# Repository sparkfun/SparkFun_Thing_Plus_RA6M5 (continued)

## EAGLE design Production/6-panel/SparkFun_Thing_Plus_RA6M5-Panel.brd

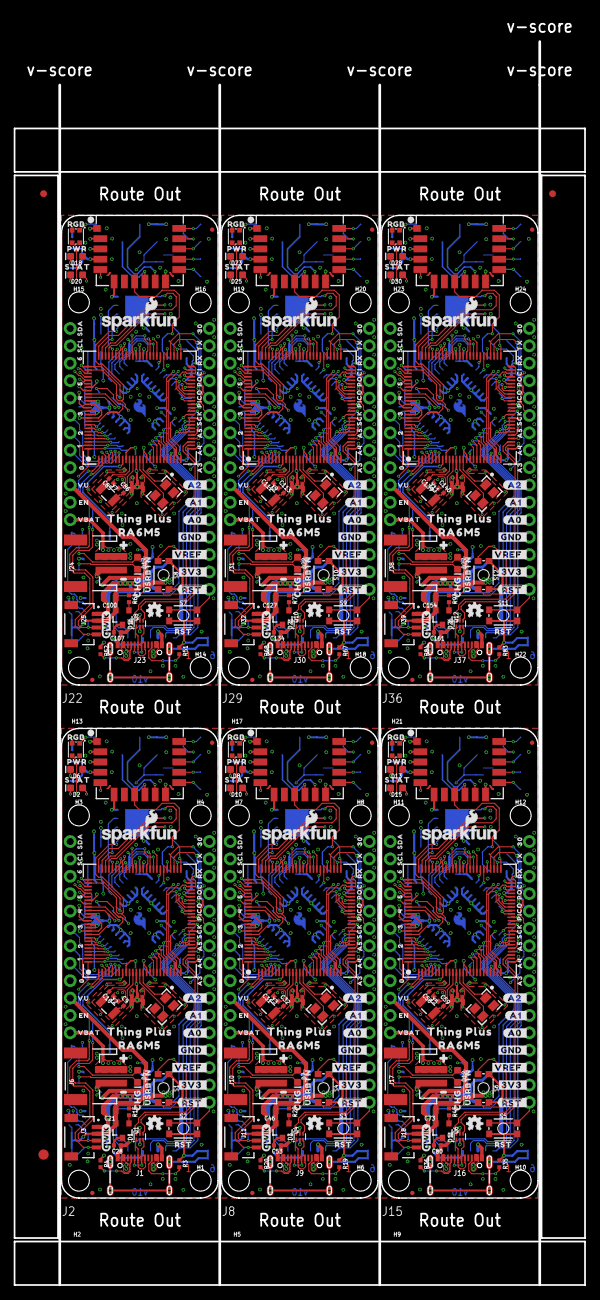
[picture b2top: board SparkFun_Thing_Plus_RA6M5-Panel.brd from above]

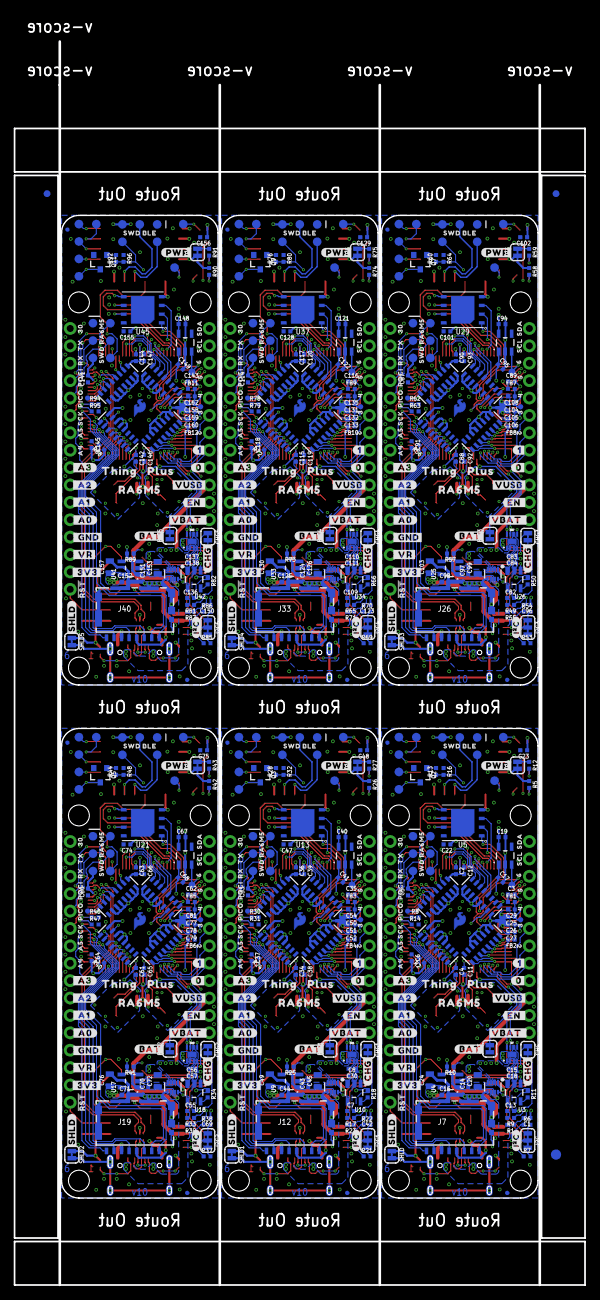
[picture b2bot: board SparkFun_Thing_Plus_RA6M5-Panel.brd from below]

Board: 6 copper layers, 83.3 x 181.6 mm, 1104 parts (657 on the bottom side), 702 nets.

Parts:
BAT, BAT1, BAT2, BAT3, BAT4, BAT5: JUMPER-SMT_2_NC_TRACE_SILK; SMT-JUMPER_2_NC_TRACE_SILK
C1, C19, C27, C29, C40, C42, C52, C54, C67, C69, C79, C81, C94, C96, C106, C108, C121, C123, C133, C135, C148, C150, C160, C162: 1.0uF; 0402-TIGHT
C2, C3, C4, C5, C6, C11, C12, C18, C22, C23, C25, C26, C28, C30, C33, C34, C35, C36, C37, C38, C39, C47, C48, C50, C51, C53, C57, C60, C61, C62, C63, C64, C65, C66, C74, C75, C77, C78, C80, C84, C87, C88, C89, C90, C91, C92, C93, C101, C102, C104, C105, C107, C111, C114, C115, C116, C117, C118, C119, C120, C128, C129, C131, C132, C134, C138, C141, C142, C143, C144, C145, C146, C147, C155, C156, C158, C159, C161: 0.1uF; 0402-TIGHT
C7, C8, C13, C14, C15, C16, C17, C41, C43, C44, C55, C56, C68, C70, C71, C82, C83, C95, C97, C98, C109, C110, C122, C124, C125, C136, C137, C149, C151, C152: 2.2uF; 0402-TIGHT
C9, C10, C31, C32, C58, C59, C85, C86, C112, C113, C139, C140: 9.1pF; 0402-TIGHT
C20, C21, C45, C46, C72, C73, C99, C100, C126, C127, C153, C154: 10uF; 0805
C24, C49, C76, C103, C130, C157: 47uF/6.3V; 0805
CHG, CHG1, CHG2, CHG3, CHG4, CHG5: JUMPER-SMT_2_NC_TRACE_SILK; SMT-JUMPER_2_NC_TRACE_SILK
D1, D3, D11, D16, D21, D26: PRTR5V0U2F; SOT886
D2, D10, D15, D20, D25, D30: BLUE; LED-0603
D4, D9, D14, D19, D24, D29: WS2812_2020; WS2812-2020
D5, D7, D12, D17, D22, D27: Yellow; LED-0603
D6, D8, D13, D18, D23, D28: LED-0603
E$1, E$2, E$3, E$4: FIDUCIAL-1X2
E$5, E$6: FIDUCIAL-1.5X3
FB1, FB2, FB3, FB4, FB5, FB6, FB7, FB8, FB9, FB10, FB11, FB12: 120-OHM; 0402-TIGHT
FD1, FD2, FD3, FD4, FD5, FD6, FD7, FD8, FD9, FD10, FD11, FD12, FD13, FD14, FD15, FD16, FD17, FD18, FD19, FD20, FD21, FD22, FD23, FD24: FIDUCIALUFIDUCIAL; FIDUCIAL-MICRO
FRAME1, FRAME2, FRAME3, FRAME4, FRAME5, FRAME6: FRAME-LEDGERNO_FOOTPRINT; DUMMY
H1, H2, H3, H4, H5, H6, H7, H8, H9, H10, H11, H12, H13, H14, H15, H16, H17, H18, H19, H20, H21, H22, H23, H24: STAND-OFFTIGHT; STAND-OFF-TIGHT
I2C, I2C1, I2C2, I2C3, I2C4, I2C5: JUMPER-SMT_3_2-NC_TRACE_SILK; SMT-JUMPER_3_2-NC_TRACE_SILK
J1, J9, J16, J23, J30, J37: USB Female Type C Connector; USB-C-16P-6LAYER-ISOLATED
J2, J8, J15, J22, J29, J36: THING_PLUS_LOGICAL; THING_PLUS
J3, J11, J18, J25, J32, J39: QWIIC_RA; JST04_1MM_RA
J4, J13, J20, J27, J34, J41: CONN_03X2; PAD_05_03X2_TP
J5, J14, J21, J28, J35, J42: PAD_05_03X2_TP_NO4
J6, J10, J17, J24, J31, J38: JST-2-SMD
J7, J12, J19, J26, J33, J40: MICRO-SDFRICTION; MICROSD_TINY
JP1, JP2, JP3, JP4, JP5, JP6: JUMPER-SMT_2_NC_TRACE_SILK; SMT-JUMPER_2_NC_TRACE_SILK
LOGO1, LOGO7, LOGO11, LOGO15, LOGO19, LOGO23: OSHW-LOGOMINI; OSHW-LOGO-MINI
LOGO2, LOGO5, LOGO9, LOGO13, LOGO17, LOGO21: SFE_LOGO_NAME_FLAME.1_INCH; SFE_LOGO_NAME_FLAME_.1
LOGO3, LOGO6, LOGO10, LOGO14, LOGO18, LOGO22: QWIIC_LOGO_4MM; QWIIC_4MM
LOGO4, LOGO8, LOGO12, LOGO16, LOGO20, LOGO24: SFE_LOGO_NAME_FLAMEBLANK; BLANK
Q1, Q2, Q3, Q4, Q5, Q6, Q7, Q8, Q9, Q10, Q11, Q12: 20V/4.2A/52mΩ/1.4W; SOT23-3
R1, R13, R15, R23, R28, R29, R39, R44, R45, R55, R60, R61, R71, R76, R77, R87, R92, R93: 1k; 0402-TIGHT
R2, R24, R40, R56, R72, R88: 20k; 0402-TIGHT
R3, R4, R19, R20, R35, R36, R51, R52, R67, R68, R83, R84: 5.1k; 0402-TIGHT
R5, R6, R7, R21, R22, R26, R37, R38, R42, R53, R54, R58, R69, R70, R74, R85, R86, R90: 2.2k; 0402-TIGHT
R8, R14, R16, R30, R31, R32, R46, R47, R48, R62, R63, R64, R78, R79, R80, R94, R95, R96: 10k; 0402-TIGHT
R9, R11, R12, R17, R18, R27, R33, R34, R43, R49, R50, R59, R65, R66, R75, R81, R82, R91: 4.7k; 0402-TIGHT
R10, R25, R41, R57, R73, R89: 1M; 0402-TIGHT
RN1, RN2, RN3, RN4, RN5, RN6, RN7, RN8, RN9, RN10, RN11, RN12, RN13, RN14, RN15, RN16, RN17, RN18, RN19, RN20, RN21, RN22, RN23, RN24: 10K; 2506_AR
S1, S4, S6, S8, S10, S12: USER; TACTILE_SWITCH_SMD_4.6X2.8MM
S2, S3, S5, S7, S9, S11: RESET; TACTILE_SWITCH_SMD_4.6X2.8MM
SHLD, SHLD1, SHLD2, SHLD3, SHLD4, SHLD5: JUMPER-SMT_2_NC_TRACE_SILK; SMT-JUMPER_2_NC_TRACE_SILK
SUPPLYTIE1, SUPPLYTIE2, SUPPLYTIE3, SUPPLYTIE4, SUPPLYTIE5, SUPPLYTIE6, SUPPLYTIE7, SUPPLYTIE8, SUPPLYTIE9, SUPPLYTIE10, SUPPLYTIE11, SUPPLYTIE12, SUPPLYTIE13, SUPPLYTIE14, SUPPLYTIE15, SUPPLYTIE16, SUPPLYTIE17, SUPPLYTIE18: 2PT_GND_TIESMALL; 2PT_GND_TIE_SMALL
TP1, TP3, TP5, TP6, TP7, TP8, TP10, TP11, TP13, TP15, TP16, TP17, TP18, TP20, TP21, TP23, TP25, TP26, TP27, TP28, TP30, TP31, TP33, TP35, TP36, TP37, TP38, TP40, TP41, TP43, TP45, TP46, TP47, TP48, TP50, TP51, TP53, TP55, TP56, TP57, TP58, TP60: TEST-POINT3X5; PAD.03X.05
TP2, TP12, TP22, TP32, TP42, TP52: TEST-POINT3X4; PAD.03X.04
TP4, TP9, TP14, TP19, TP24, TP29, TP34, TP39, TP44, TP49, TP54, TP59: TEST-POINT3; PAD.03X.03
U1, U14, U22, U30, U38, U46: R7FA6M5; P-LQFP100-14X14-0.50
U2, U12, U20, U28, U36, U44: DA14531MOD
U3, U10, U18, U26, U34, U42: MCP73831; SOT23-5
U4, U6, U9, U15, U17, U23, U25, U31, U33, U39, U41, U47: RT9080-33GJ5; SOT23-5
U5, U13, U21, U29, U37, U45: MX25L12833F 128Mb; WSON-8-6X5
U7, U11, U19, U27, U35, U43: MAX17048; DFN-8
U8, U16, U24, U32, U40, U48: LM66200; SOT8
U$1, U$3, U$155, U$232, U$309, U$386: #I�C#0
U$2, U$4, U$156, U$233, U$310, U$387: #CHG#0
U$5, U$8, U$157, U$234, U$311, U$388: SFE_LOGO_FLAME_COPPER_EXPOSED_.1
U$6, U$13, U$51, U$109, U$158, U$186, U$235, U$263, U$312, U$340, U$389, U$417: #RST#0
U$7, U$14, U$159, U$236, U$313, U$390: CHG0
U$9, U$130, U$207, U$284, U$361, U$438: SWD_RA6M50
U$10, U$131, U$208, U$285, U$362, U$439: SWD_BLE0
U$11, U$15, U$160, U$237, U$314, U$391: STAT0
U$12, U$86, U$137, U$138, U$214, U$215, U$291, U$292, U$368, U$369, U$445, U$446: 300
U$16, U$74, U$161, U$238, U$315, U$392: PWR0
U$17, U$75, U$162, U$239, U$316, U$393: RGB0
U$18, U$128, U$205, U$282, U$359, U$436: THING_PLUS0
U$19, U$80, U$163, U$240, U$317, U$394: ##RST#_#0
U$20, U$87, U$164, U$241, U$318, U$395: #3V3_#0
U$21, U$88, U$165, U$242, U$319, U$396: #VREF_#0
U$22, U$89, U$166, U$243, U$320, U$397: #GND_#0
U$23, U$90, U$167, U$244, U$321, U$398: #A0_#0
U$24, U$91, U$168, U$245, U$322, U$399: #A1_#0
U$25, U$92, U$169, U$246, U$323, U$400: #A2_#0
U$26, U$93, U$170, U$247, U$324, U$401: A30
U$27, U$59, U$94, U$116, U$171, U$193, U$248, U$270, U$325, U$347, U$402, U$424: A40
U$28, U$60, U$95, U$117, U$172, U$194, U$249, U$271, U$326, U$348, U$403, U$425: A50
U$29, U$61, U$96, U$118, U$173, U$195, U$250, U$272, U$327, U$349, U$404, U$426: SCK0
U$30, U$62, U$97, U$119, U$174, U$196, U$251, U$273, U$328, U$350, U$405, U$427: PICO0
U$31, U$63, U$98, U$120, U$175, U$197, U$252, U$274, U$329, U$351, U$406, U$428: POCI0
U$32, U$64, U$99, U$121, U$176, U$198, U$253, U$275, U$330, U$352, U$407, U$429: RX0
U$33, U$65, U$100, U$122, U$177, U$199, U$254, U$276, U$331, U$353, U$408, U$430: TX0
U$34, U$43, U$139, U$146, U$216, U$223, U$293, U$300, U$370, U$377, U$447, U$454: 60
U$35, U$67, U$101, U$123, U$178, U$200, U$255, U$277, U$332, U$354, U$409, U$431: SDA0
U$36, U$68, U$102, U$124, U$179, U$201, U$256, U$278, U$333, U$355, U$410, U$432: SCL0
U$37, U$48, U$140, U$147, U$217, U$224, U$294, U$301, U$371, U$378, U$448, U$455: 50
U$38, U$66, U$141, U$148, U$218, U$225, U$295, U$302, U$372, U$379, U$449, U$456: 40
U$39, U$69, U$142, U$149, U$219, U$226, U$296, U$303, U$373, U$380, U$450, U$457: 30
U$40, U$70, U$143, U$150, U$220, U$227, U$297, U$304, U$374, U$381, U$451, U$458: 20
U$41, U$144, U$221, U$298, U$375, U$452: 10
U$42, U$145, U$222, U$299, U$376, U$453: 00
U$44, U$103, U$180, U$257, U$334, U$411: VU0
U$45, U$104, U$181, U$258, U$335, U$412: EN0
U$46, U$105, U$182, U$259, U$336, U$413: VBAT0
U$47, U$106, U$183, U$260, U$337, U$414: #PWR#0
U$49, U$107, U$184, U$261, U$338, U$415: #BAT#0
U$50, U$108, U$185, U$262, U$339, U$416: #SHLD#0
U$52, U$110, U$187, U$264, U$341, U$418: #_3V3#0
U$53, U$154, U$231, U$308, U$385, U$462: #_VR#0
U$54, U$111, U$188, U$265, U$342, U$419: #_GND#0
U$55, U$112, U$189, U$266, U$343, U$420: #_A0#0
U$56, U$113, U$190, U$267, U$344, U$421: #_A1#0
U$57, U$114, U$191, U$268, U$345, U$422: #_A2#0
U$58, U$115, U$192, U$269, U$346, U$423: #_A3#0
U$71, U$151, U$228, U$305, U$382, U$459: #1#0
U$72, U$152, U$229, U$306, U$383, U$460: #0#0
U$73, U$153, U$230, U$307, U$384, U$461: #USRBTN#0
U$76, U$125, U$202, U$279, U$356, U$433: #VUSB#0
U$77, U$126, U$203, U$280, U$357, U$434: #EN_#0
U$78, U$127, U$204, U$281, U$358, U$435: #VBAT_#0
U$79, U$82, U$129, U$132, U$206, U$209, U$283, U$286, U$360, U$363, U$437, U$440: RA6M50
U$81, U$135, U$212, U$289, U$366, U$443: #0
U$83, U$133, U$210, U$287, U$364, U$441: THING0
U$84, U$134, U$211, U$288, U$365, U$442: PLUS0
U$85, U$136, U$213, U$290, U$367, U$444: _#0
Y1, Y4, Y6, Y8, Y10, Y12: 24.000MHz; 4-SMD,32X25
Y2, Y3, Y5, Y7, Y9, Y11: 32.768kHz; CRYSTAL-SMD-3.2X1.5MM

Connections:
3.3V: BAT.1, C2.1, C3.1, C4.1, C5.1, C6.1, C16.1, C21.1, C22.2, C23.2, C24.1, D4.VCC, D6.A, FB1.1, I2C.2, J2.27, J3.2, J4.1, J5.1, Q1.2, Q2.2, R8.2, R14.2, R16.1, RN1.10, RN1.11, RN3.1, RN3.2, RN3.3, RN4.1, RN5.15, RN5.16, U1.15, U1.29, U1.46, U1.62, U1.82, U2.7, U4.5, U5.8
3.3V1: BAT1.1, C33.1, C34.1, C35.1, C36.1, C37.1, C44.1, C46.1, C47.2, C48.2, C49.1, D8.A, D9.VCC, FB3.1, I2C1.2, J8.27, J11.2, J13.1, J14.1, Q3.2, Q4.2, R30.2, R31.2, R32.1, RN2.1, RN6.10, RN6.11, RN7.15, RN7.16, RN8.1, RN8.2, RN8.3, U9.5, U12.7, U13.8, U14.15, U14.29, U14.46, U14.62, U14.82
3.3V2: BAT2.1, C60.1, C61.1, C62.1, C63.1, C64.1, C71.1, C73.1, C74.2, C75.2, C76.1, D13.A, D14.VCC, FB5.1, I2C2.2, J15.27, J18.2, J20.1, J21.1, Q5.2, Q6.2, R46.2, R47.2, R48.1, RN9.1, RN10.10, RN10.11, RN11.15, RN11.16, RN12.1, RN12.2, RN12.3, U17.5, U20.7, U21.8, U22.15, U22.29, U22.46, U22.62, U22.82
3.3V3: BAT3.1, C87.1, C88.1, C89.1, C90.1, C91.1, C98.1, C100.1, C101.2, C102.2, C103.1, D18.A, D19.VCC, FB7.1, I2C3.2, J22.27, J25.2, J27.1, J28.1, Q7.2, Q8.2, R62.2, R63.2, R64.1, RN13.1, RN14.10, RN14.11, RN15.15, RN15.16, RN16.1, RN16.2, RN16.3, U25.5, U28.7, U29.8, U30.15, U30.29, U30.46, U30.62, U30.82
3.3V4: BAT4.1, C114.1, C115.1, C116.1, C117.1, C118.1, C125.1, C127.1, C128.2, C129.2, C130.1, D23.A, D24.VCC, FB9.1, I2C4.2, J29.27, J32.2, J34.1, J35.1, Q9.2, Q10.2, R78.2, R79.2, R80.1, RN17.1, RN18.10, RN18.11, RN19.15, RN19.16, RN20.1, RN20.2, RN20.3, U33.5, U36.7, U37.8, U38.15, U38.29, U38.46, U38.62, U38.82
3.3V5: BAT5.1, C141.1, C142.1, C143.1, C144.1, C145.1, C152.1, C154.1, C155.2, C156.2, C157.1, D28.A, D29.VCC, FB11.1, I2C5.2, J36.27, J39.2, J41.1, J42.1, Q11.2, Q12.2, R94.2, R95.2, R96.1, RN21.1, RN22.10, RN22.11, RN23.15, RN23.16, RN24.1, RN24.2, RN24.3, U41.5, U44.7, U45.8, U46.15, U46.29, U46.46, U46.62, U46.82
3.3V_SW: C28.2, J7.4, Q1.3
3.3V_SW1: C53.2, J12.4, Q4.3
3.3V_SW2: C80.2, J19.4, Q6.3
3.3V_SW3: C107.2, J26.4, Q8.3
3.3V_SW4: C134.2, J33.4, Q10.3
3.3V_SW5: C161.2, J40.4, Q12.3
!CTS_RA6/RTS_DA14531!: TP7.1, U1.47, U2.13
!CTS_RA6/RTS_DA14531!1: TP17.1, U12.13, U14.47
!CTS_RA6/RTS_DA14531!2: TP27.1, U20.13, U22.47
!CTS_RA6/RTS_DA14531!3: TP37.1, U28.13, U30.47
!CTS_RA6/RTS_DA14531!4: TP47.1, U36.13, U38.47
!CTS_RA6/RTS_DA14531!5: TP57.1, U44.13, U46.47
!DA14531_RST!: J5.6, R13.1, R16.2, U1.58
!DA14531_RST!1: J14.6, R28.1, R32.2, U14.58
!DA14531_RST!2: J21.6, R44.1, R48.2, U22.58
!DA14531_RST!3: J28.6, R60.1, R64.2, U30.58
!DA14531_RST!4: J35.6, R76.1, R80.2, U38.58
!DA14531_RST!5: J42.6, R92.1, R96.2, U46.58
!FG_ALRT!: RN5.1, U1.100, U7.5
!FG_ALRT!1: RN7.1, U11.5, U14.100
!FG_ALRT!2: RN11.1, U19.5, U22.100
!FG_ALRT!3: RN15.1, U27.5, U30.100
!FG_ALRT!4: RN19.1, U35.5, U38.100
!FG_ALRT!5: RN23.1, U43.5, U46.100
!NMI!: RN4.16, TP9.1, U1.40
!NMI!1: RN2.16, TP19.1, U14.40
!NMI!2: RN9.16, TP29.1, U22.40
!NMI!3: RN13.16, TP39.1, U30.40
!NMI!4: RN17.16, TP49.1, U38.40
!NMI!5: RN21.16, TP59.1, U46.40
!QCS!: RN1.7, U1.77, U5.1
!QCS!1: RN6.7, U13.1, U14.77
!QCS!2: RN10.7, U21.1, U22.77
!QCS!3: RN14.7, U29.1, U30.77
!QCS!4: RN18.7, U37.1, U38.77
!QCS!5: RN22.7, U45.1, U46.77
!RA6M5_RESET!: J2.28, J4.6, R14.1, S2.3, S2.4, U1.38, U2.8
!RA6M5_RESET!1: J8.28, J13.6, R31.1, S3.3, S3.4, U12.8, U14.38
!RA6M5_RESET!2: J15.28, J20.6, R47.1, S5.3, S5.4, U20.8, U22.38
!RA6M5_RESET!3: J22.28, J27.6, R63.1, S7.3, S7.4, U28.8, U30.38
!RA6M5_RESET!4: J29.28, J34.6, R79.1, S9.3, S9.4, U36.8, U38.38
!RA6M5_RESET!5: J36.28, J41.6, R95.1, S11.3, S11.4, U44.8, U46.38
!RTS_RA6/CTS_DA14531!: TP8.1, U1.49, U2.16
!RTS_RA6/CTS_DA14531!1: TP18.1, U12.16, U14.49
!RTS_RA6/CTS_DA14531!2: TP28.1, U20.16, U22.49
!RTS_RA6/CTS_DA14531!3: TP38.1, U28.16, U30.49
!RTS_RA6/CTS_DA14531!4: TP48.1, U36.16, U38.49
!RTS_RA6/CTS_DA14531!5: TP58.1, U44.16, U46.49
!SD_EN!: R15.1, RN3.16, U1.16
!SD_EN!1: R29.1, RN8.16, U14.16
!SD_EN!2: R45.1, RN12.16, U22.16
!SD_EN!3: R61.1, RN16.16, U30.16
!SD_EN!4: R77.1, RN20.16, U38.16
!SD_EN!5: R93.1, RN24.16, U46.16
!USR_BTN!: RN3.15, S1.1, S1.2, U1.17
!USR_BTN!1: RN8.15, S4.1, S4.2, U14.17
!USR_BTN!2: RN12.15, S6.1, S6.2, U22.17
!USR_BTN!3: RN16.15, S8.1, S8.2, U30.17
!USR_BTN!4: RN20.15, S10.1, S10.2, U38.17
!USR_BTN!5: RN24.15, S12.1, S12.2, U46.17
A0/DAC0/D1: J8.24, U14.85
A0/DAC0/D2: J15.24, U22.85
A0/DAC0/D3: J22.24, U30.85
A0/DAC0/D4: J29.24, U38.85
A0/DAC0/D5: J36.24, U46.85
A0/DAC0/D7: J2.24, U1.85
A1/DAC1/D1: J8.23, U14.84
A1/DAC1/D2: J15.23, U22.84
A1/DAC1/D3: J22.23, U30.84
A1/DAC1/D4: J29.23, U38.84
A1/DAC1/D5: J36.23, U46.84
A1/DAC1/D8: J2.23, U1.84
A2/D1: J8.22, U14.81
A2/D2: J15.22, U22.81
A2/D3: J22.22, U30.81
A2/D4: J29.22, U38.81
A2/D5: J36.22, U46.81
A2/D9: J2.22, U1.81
A3/D1: J8.21, U14.80
A3/D2: J15.21, U22.80
A3/D3: J22.21, U30.80
A3/D4: J29.21, U38.80
A3/D5: J36.21, U46.80
A3/D10: J2.21, U1.80
A4/D1: J8.20, U14.79
A4/D2: J15.20, U22.79
A4/D3: J22.20, U30.79
A4/D4: J29.20, U38.79
A4/D5: J36.20, U46.79
A4/D11: J2.20, U1.79
A5/D1: J8.19, U14.78
A5/D2: J15.19, U22.78
A5/D3: J22.19, U30.78
A5/D4: J29.19, U38.78
A5/D5: J36.19, U46.78
A5/D12: J2.19, U1.78
AGND: C25.2, C26.2, C27.2, C29.2, SUPPLYTIE1.P$1, U1.86, U1.89, U1.90
AGND1: C50.2, C51.2, C52.2, C54.2, SUPPLYTIE6.P$1, U14.86, U14.89, U14.90
AGND2: C77.2, C78.2, C79.2, C81.2, SUPPLYTIE9.P$1, U22.86, U22.89, U22.90
AGND3: C104.2, C105.2, C106.2, C108.2, SUPPLYTIE12.P$1, U30.86, U30.89, U30.90
AGND4: C131.2, C132.2, C133.2, C135.2, SUPPLYTIE15.P$1, U38.86, U38.89, U38.90
AGND5: C158.2, C159.2, C160.2, C162.2, SUPPLYTIE18.P$1, U46.86, U46.89, U46.90
AVCC0: C25.1, C29.1, FB1.2, TP4.1, U1.88
AVCC1: C50.1, C54.1, FB3.2, TP14.1, U14.88
AVCC2: C77.1, C81.1, FB5.2, TP24.1, U22.88
AVCC3: C104.1, C108.1, FB7.2, TP34.1, U30.88
AVCC4: C131.1, C135.1, FB9.2, TP44.1, U38.88
AVCC5: C158.1, C162.1, FB11.2, TP54.1, U46.88
BAT_SW: RN5.2, U1.99, U8.8
BAT_SW1: RN7.2, U14.99, U16.8
BAT_SW2: RN11.2, U22.99, U24.8
BAT_SW3: RN15.2, U30.99, U32.8
BAT_SW4: RN19.2, U38.99, U40.8
BAT_SW5: RN23.2, U46.99, U48.8
BLE_RST: Q2.3, TP3.1, U2.12
BLE_RST1: Q3.3, TP13.1, U12.12
BLE_RST2: Q5.3, TP23.1, U20.12
BLE_RST3: Q7.3, TP33.1, U28.12
BLE_RST4: Q9.3, TP43.1, U36.12
BLE_RST5: Q11.3, TP53.1, U44.12
BOOT/MD: R8.1, TP10.1, U1.39, U2.15
BOOT/MD1: R30.1, TP20.1, U12.15, U14.39
BOOT/MD2: R46.1, TP30.1, U20.15, U22.39
BOOT/MD3: R62.1, TP40.1, U28.15, U30.39
BOOT/MD4: R78.1, TP50.1, U36.15, U38.39
BOOT/MD5: R94.1, TP60.1, U44.15, U46.39
DA14531_SWCLK: J5.3, U2.10
DA14531_SWCLK1: J14.3, U12.10
DA14531_SWCLK2: J21.3, U20.10
DA14531_SWCLK3: J28.3, U28.10
DA14531_SWCLK4: J35.3, U36.10
DA14531_SWCLK5: J42.3, U44.10
DA14531_SWDIO: J5.2, U2.9
DA14531_SWDIO1: J14.2, U12.9
DA14531_SWDIO2: J21.2, U20.9
DA14531_SWDIO3: J28.2, U28.9
DA14531_SWDIO4: J35.2, U36.9
DA14531_SWDIO5: J42.2, U44.9
EXTAL: U1.14, Y1.1
EXTAL1: U14.14, Y4.1
EXTAL2: U22.14, Y6.1
EXTAL3: U30.14, Y8.1
EXTAL4: U38.14, Y10.1
EXTAL5: U46.14, Y12.1
FREE/D1: J8.13, U14.44
FREE/D2: J15.13, U22.44
FREE/D3: J22.13, U30.44
FREE/D4: J29.13, U38.44
FREE/D5: J36.13, U46.44
FREE/D30: J2.13, U1.44
GND: C1.1, C2.2, C3.2, C4.2, C5.2, C6.2, C11.2, C12.2, C13.2, C14.2, C15.2, C16.2, C17.2, C18.1, C19.2, C20.2, C21.2, C22.1, C23.1, C24.2, C28.1, D1.2, D4.GND, J1.GND, J1.GND2, J2.25, J3.1, J4.5, J5.5, J6.1, J7.6, J7.GND1, J7.GND2, J7.GND3, J7.GND4, J7.GND5, J7.GND6, JP4.1, R2.1, R3.1, R4.1, R5.1, R11.1, RN1.1, RN1.2, RN1.3, RN1.4, RN1.5, RN1.8, RN3.4, RN3.5, RN3.6, RN3.8, RN4.2, RN4.3, RN4.4, RN4.5, RN4.6, RN4.7, RN4.8, RN4.9, RN5.9, RN5.10, RN5.11, RN5.12, RN5.13, RN5.14, S1.3, S1.4, S2.1, S2.2, SHLD.1, SUPPLYTIE1.P$2, SUPPLYTIE2.P$2, SUPPLYTIE3.P$1, U1.12, U1.26, U1.45, U1.63, U1.83, U2.1, U2.2, U2.3, U2.4, U2.6, U2.11, U3.2, U4.2, U5.4, U6.2, U7.1, U7.4, U7.6, U7.9, U8.1, U8.4, U8.5
GND1: C7.2, C8.2, C30.1, C33.2, C34.2, C35.2, C36.2, C37.2, C38.2, C39.2, C40.2, C41.2, C42.1, C43.2, C44.2, C45.2, C46.2, C47.1, C48.1, C49.2, C53.1, D3.2, D9.GND, J8.25, J9.GND, J9.GND2, J10.1, J11.1, J12.6, J12.GND1, J12.GND2, J12.GND3, J12.GND4, J12.GND5, J12.GND6, J13.5, J14.5, JP1.1, R18.1, R19.1, R20.1, R24.1, R26.1, RN2.2, RN2.3, RN2.4, RN2.5, RN2.6, RN2.7, RN2.8, RN2.9, RN6.1, RN6.2, RN6.3, RN6.4, RN6.5, RN6.8, RN7.9, RN7.10, RN7.11, RN7.12, RN7.13, RN7.14, RN8.4, RN8.5, RN8.6, RN8.8, S3.1, S3.2, S4.3, S4.4, SHLD1.1, SUPPLYTIE4.P$1, SUPPLYTIE5.P$2, SUPPLYTIE6.P$2, U9.2, U10.2, U11.1, U11.4, U11.6, U11.9, U12.1, U12.2, U12.3, U12.4, U12.6, U12.11, U13.4, U14.12, U14.26, U14.45, U14.63, U14.83, U15.2, U16.1, U16.4, U16.5
GND2: C55.2, C56.2, C57.1, C60.2, C61.2, C62.2, C63.2, C64.2, C65.2, C66.2, C67.2, C68.2, C69.1, C70.2, C71.2, C72.2, C73.2, C74.1, C75.1, C76.2, C80.1, D11.2, D14.GND, J15.25, J16.GND, J16.GND2, J17.1, J18.1, J19.6, J19.GND1, J19.GND2, J19.GND3, J19.GND4, J19.GND5, J19.GND6, J20.5, J21.5, JP2.1, R34.1, R35.1, R36.1, R40.1, R42.1, RN9.2, RN9.3, RN9.4, RN9.5, RN9.6, RN9.7, RN9.8, RN9.9, RN10.1, RN10.2, RN10.3, RN10.4, RN10.5, RN10.8, RN11.9, RN11.10, RN11.11, RN11.12, RN11.13, RN11.14, RN12.4, RN12.5, RN12.6, RN12.8, S5.1, S5.2, S6.3, S6.4, SHLD2.1, SUPPLYTIE7.P$1, SUPPLYTIE8.P$2, SUPPLYTIE9.P$2, U17.2, U18.2, U19.1, U19.4, U19.6, U19.9, U20.1, U20.2, U20.3, U20.4, U20.6, U20.11, U21.4, U22.12, U22.26, U22.45, U22.63, U22.83, U23.2, U24.1, U24.4, U24.5
GND3: C82.2, C83.2, C84.1, C87.2, C88.2, C89.2, C90.2, C91.2, C92.2, C93.2, C94.2, C95.2, C96.1, C97.2, C98.2, C99.2, C100.2, C101.1, C102.1, C103.2, C107.1, D16.2, D19.GND, J22.25, J23.GND, J23.GND2, J24.1, J25.1, J26.6, J26.GND1, J26.GND2, J26.GND3, J26.GND4, J26.GND5, J26.GND6, J27.5, J28.5, JP3.1, R50.1, R51.1, R52.1, R56.1, R58.1, RN13.2, RN13.3, RN13.4, RN13.5, RN13.6, RN13.7, RN13.8, RN13.9, RN14.1, RN14.2, RN14.3, RN14.4, RN14.5, RN14.8, RN15.9, RN15.10, RN15.11, RN15.12, RN15.13, RN15.14, RN16.4, RN16.5, RN16.6, RN16.8, S7.1, S7.2, S8.3, S8.4, SHLD3.1, SUPPLYTIE10.P$1, SUPPLYTIE11.P$2, SUPPLYTIE12.P$2, U25.2, U26.2, U27.1, U27.4, U27.6, U27.9, U28.1, U28.2, U28.3, U28.4, U28.6, U28.11, U29.4, U30.12, U30.26, U30.45, U30.63, U30.83, U31.2, U32.1, U32.4, U32.5
GND4: C109.2, C110.2, C111.1, C114.2, C115.2, C116.2, C117.2, C118.2, C119.2, C120.2, C121.2, C122.2, C123.1, C124.2, C125.2, C126.2, C127.2, C128.1, C129.1, C130.2, C134.1, D21.2, D24.GND, J29.25, J30.GND, J30.GND2, J31.1, J32.1, J33.6, J33.GND1, J33.GND2, J33.GND3, J33.GND4, J33.GND5, J33.GND6, J34.5, J35.5, JP5.1, R66.1, R67.1, R68.1, R72.1, R74.1, RN17.2, RN17.3, RN17.4, RN17.5, RN17.6, RN17.7, RN17.8, RN17.9, RN18.1, RN18.2, RN18.3, RN18.4, RN18.5, RN18.8, RN19.9, RN19.10, RN19.11, RN19.12, RN19.13, RN19.14, RN20.4, RN20.5, RN20.6, RN20.8, S9.1, S9.2, S10.3, S10.4, SHLD4.1, SUPPLYTIE13.P$1, SUPPLYTIE14.P$2, SUPPLYTIE15.P$2, U33.2, U34.2, U35.1, U35.4, U35.6, U35.9, U36.1, U36.2, U36.3, U36.4, U36.6, U36.11, U37.4, U38.12, U38.26, U38.45, U38.63, U38.83, U39.2, U40.1, U40.4, U40.5
GND5: C136.2, C137.2, C138.1, C141.2, C142.2, C143.2, C144.2, C145.2, C146.2, C147.2, C148.2, C149.2, C150.1, C151.2, C152.2, C153.2, C154.2, C155.1, C156.1, C157.2, C161.1, D26.2, D29.GND, J36.25, J37.GND, J37.GND2, J38.1, J39.1, J40.6, J40.GND1, J40.GND2, J40.GND3, J40.GND4, J40.GND5, J40.GND6, J41.5, J42.5, JP6.1, R82.1, R83.1, R84.1, R88.1, R90.1, RN21.2, RN21.3, RN21.4, RN21.5, RN21.6, RN21.7, RN21.8, RN21.9, RN22.1, RN22.2, RN22.3, RN22.4, RN22.5, RN22.8, RN23.9, RN23.10, RN23.11, RN23.12, RN23.13, RN23.14, RN24.4, RN24.5, RN24.6, RN24.8, S11.1, S11.2, S12.3, S12.4, SHLD5.1, SUPPLYTIE16.P$1, SUPPLYTIE17.P$2, SUPPLYTIE18.P$2, U41.2, U42.2, U43.1, U43.4, U43.6, U43.9, U44.1, U44.2, U44.3, U44.4, U44.6, U44.11, U45.4, U46.12, U46.26, U46.45, U46.63, U46.83, U47.2, U48.1, U48.4, U48.5
GND_7: C31.1, C32.1, SUPPLYTIE5.P$1
GND_15: C58.1, C59.1, SUPPLYTIE8.P$1
GND_23: C85.1, C86.1, SUPPLYTIE11.P$1
GND_32: C9.1, C10.1, SUPPLYTIE2.P$1
GND_33: C112.1, C113.1, SUPPLYTIE14.P$1
GND_41: C139.1, C140.1, SUPPLYTIE17.P$1
GPIO0/!CS!/D0: J2.9, U1.55
GPIO0/!CS!/D1: J8.9, U14.55
GPIO0/!CS!/D2: J15.9, U22.55
GPIO0/!CS!/D3: J22.9, U30.55
GPIO0/!CS!/D4: J29.9, U38.55
GPIO0/!CS!/D5: J36.9, U46.55
GPIO1/D1: J2.8, U1.7
GPIO1/D2: J8.8, U14.7
GPIO1/D3: J15.8, U22.7
GPIO1/D4: J22.8, U30.7
GPIO1/D5: J29.8, U38.7
GPIO1/D6: J36.8, U46.7
GPIO2/D1: J8.7, U14.6
GPIO2/D2: J2.7, U1.6
GPIO2/D3: J15.7, U22.6
GPIO2/D4: J22.7, U30.6
GPIO2/D5: J29.7, U38.6
GPIO2/D6: J36.7, U46.6
GPIO3/D1: J8.6, U14.5
GPIO3/D2: J15.6, U22.5
GPIO3/D3: J2.6, U1.5
GPIO3/D4: J22.6, U30.5
GPIO3/D5: J29.6, U38.5
GPIO3/D6: J36.6, U46.5
GPIO4/D1: J8.5, U14.4
GPIO4/D2: J15.5, U22.4
GPIO4/D3: J22.5, U30.4
GPIO4/D4: J2.5, U1.4
GPIO4/D5: J29.5, U38.4
GPIO4/D6: J36.5, U46.4
GPIO5/D1: J8.4, U14.3
GPIO5/D2: J15.4, U22.3
GPIO5/D3: J22.4, U30.3
GPIO5/D4: J29.4, U38.3
GPIO5/D5: J2.4, U1.3
GPIO5/D6: J36.4, U46.3
GPIO6/D1: J8.3, U14.30
GPIO6/D2: J15.3, U22.30
GPIO6/D3: J22.3, U30.30
GPIO6/D4: J29.3, U38.30
GPIO6/D5: J36.3, U46.30
GPIO6/D6: J2.3, U1.30
unnamed: CHG.2, R9.1
unnamed: CHG.1, D5.A
unnamed: D5.C, U3.1
unnamed: Q2.1, R13.2
unnamed: R11.2, U3.5
unnamed: D2.C, R5.2
unnamed: RN1.9, U1.92
unnamed: RN3.9, U1.36
unnamed: C1.2, R1.1, RN3.7
unnamed: I2C.1, R6.2
unnamed: I2C.3, R7.2
unnamed: CHG1.2, R17.1
unnamed: RN3.14, U1.18
unnamed: JP4.2, R12.1
unnamed: R2.2, RN3.10, U1.25
unnamed: D6.C, R12.2
unnamed: RN1.14, U1.61
unnamed: RN1.15, U1.60
unnamed: J1.SHLD1, J1.SHLD2, J1.SHLD3, J1.SHLD4, J1.SHLD5, J1.SHLD6, J1.SHLD7, J1.SHLD8, SHLD.2
unnamed: J1.B5, R3.2
unnamed: J1.A5, R4.2
unnamed: RN1.16, U1.59
unnamed: RN4.15, U1.43
unnamed: RN1.13, U1.67
unnamed: CHG1.1, D7.A
unnamed: RN3.13, U1.19
unnamed: RN3.12, U1.20
unnamed: RN3.11, U1.21
unnamed: C26.1, C27.1, FB2.1, U1.87, U1.91
unnamed: RN4.13, U1.41
unnamed: RN4.12, U1.48
unnamed: RN4.14, U1.42
unnamed: BAT.2, U1.8
unnamed: D7.C, U10.1
unnamed: RN4.10, U1.57
unnamed: RN4.11, U1.56
unnamed: RN1.12, U1.68
unnamed: R18.2, U10.5
unnamed: I2C1.1, R22.2
unnamed: I2C1.3, R21.2
unnamed: RN5.8, U1.93
unnamed: RN5.7, U1.94
unnamed: RN5.6, U1.95
unnamed: RN5.5, U1.96
unnamed: RN5.4, U1.97
unnamed: RN5.3, U1.98
unnamed: Q1.1, R15.2
unnamed: J9.SHLD1, J9.SHLD2, J9.SHLD3, J9.SHLD4, J9.SHLD5, J9.SHLD6, J9.SHLD7, J9.SHLD8, SHLD1.2
unnamed: J9.B5, R19.2
unnamed: J9.A5, R20.2
unnamed: C38.1, U14.9
unnamed: C39.1, U14.64
unnamed: C42.2, R23.1, RN8.7
unnamed: R24.2, RN8.10, U14.25
unnamed: D10.C, R26.2
unnamed: JP1.2, R27.1
unnamed: D8.C, R27.2
unnamed: RN6.13, U14.67
unnamed: RN8.13, U14.19
unnamed: RN8.12, U14.20
unnamed: RN8.11, U14.21
unnamed: RN2.10, U14.57
unnamed: RN2.11, U14.56
unnamed: RN6.12, U14.68
unnamed: RN7.7, U14.94
unnamed: RN7.6, U14.95
unnamed: RN7.5, U14.96
unnamed: RN7.4, U14.97
unnamed: RN7.3, U14.98
unnamed: RN2.12, U14.48
unnamed: RN2.14, U14.42
unnamed: RN7.8, U14.93
unnamed: Q3.1, R28.2
unnamed: Q4.1, R29.2
unnamed: C51.1, C52.1, FB4.1, U14.87, U14.91
unnamed: BAT1.2, U14.8
unnamed: RN8.9, U14.36
unnamed: RN8.14, U14.18
unnamed: RN6.9, U14.92
unnamed: RN6.14, U14.61
unnamed: RN6.15, U14.60
unnamed: RN6.16, U14.59
unnamed: RN2.15, U14.43
unnamed: RN2.13, U14.41
unnamed: CHG2.2, R33.1
unnamed: CHG2.1, D12.A
unnamed: D12.C, U18.1
unnamed: R34.2, U18.5
unnamed: I2C2.1, R38.2
unnamed: I2C2.3, R37.2
unnamed: J16.SHLD1, J16.SHLD2, J16.SHLD3, J16.SHLD4, J16.SHLD5, J16.SHLD6, J16.SHLD7, J16.SHLD8, SHLD2.2
unnamed: J16.B5, R35.2
unnamed: J16.A5, R36.2
unnamed: C65.1, U22.9
unnamed: C66.1, U22.64
unnamed: C69.2, R39.1, RN12.7
unnamed: C11.1, U1.9
unnamed: C12.1, U1.64
unnamed: R40.2, RN12.10, U22.25
unnamed: D15.C, R42.2
unnamed: JP2.2, R43.1
unnamed: D13.C, R43.2
unnamed: RN10.13, U22.67
unnamed: RN12.13, U22.19
unnamed: RN12.12, U22.20
unnamed: RN12.11, U22.21
unnamed: RN9.10, U22.57
unnamed: RN9.11, U22.56
unnamed: RN10.12, U22.68
unnamed: RN11.7, U22.94
unnamed: RN11.6, U22.95
unnamed: RN11.5, U22.96
unnamed: RN11.4, U22.97
unnamed: RN11.3, U22.98
unnamed: RN9.12, U22.48
unnamed: RN9.14, U22.42
unnamed: RN11.8, U22.93
unnamed: Q5.1, R44.2
unnamed: Q6.1, R45.2
unnamed: C78.1, C79.1, FB6.1, U22.87, U22.91
unnamed: BAT2.2, U22.8
unnamed: RN12.9, U22.36
unnamed: RN12.14, U22.18
unnamed: RN10.9, U22.92
unnamed: RN10.14, U22.61
unnamed: RN10.15, U22.60
unnamed: RN10.16, U22.59
unnamed: RN9.15, U22.43
unnamed: RN9.13, U22.41
unnamed: CHG3.2, R49.1
unnamed: CHG3.1, D17.A
unnamed: D17.C, U26.1
unnamed: R50.2, U26.5
unnamed: I2C3.1, R54.2
unnamed: I2C3.3, R53.2
unnamed: J23.SHLD1, J23.SHLD2, J23.SHLD3, J23.SHLD4, J23.SHLD5, J23.SHLD6, J23.SHLD7, J23.SHLD8, SHLD3.2
unnamed: J23.B5, R51.2
unnamed: J23.A5, R52.2
unnamed: C92.1, U30.9
unnamed: C93.1, U30.64
unnamed: C96.2, R55.1, RN16.7
unnamed: R56.2, RN16.10, U30.25
unnamed: D20.C, R58.2
unnamed: JP3.2, R59.1
unnamed: D18.C, R59.2
unnamed: RN14.13, U30.67
unnamed: RN16.13, U30.19
unnamed: RN16.12, U30.20
unnamed: RN16.11, U30.21
unnamed: RN13.10, U30.57
unnamed: RN13.11, U30.56
unnamed: RN14.12, U30.68
unnamed: RN15.7, U30.94
unnamed: RN15.6, U30.95
unnamed: RN15.5, U30.96
unnamed: RN15.4, U30.97
unnamed: RN15.3, U30.98
unnamed: RN13.12, U30.48
unnamed: RN13.14, U30.42
unnamed: RN15.8, U30.93
unnamed: Q7.1, R60.2
unnamed: Q8.1, R61.2
unnamed: C105.1, C106.1, FB8.1, U30.87, U30.91
unnamed: BAT3.2, U30.8
unnamed: RN16.9, U30.36
unnamed: RN16.14, U30.18
unnamed: RN14.9, U30.92
unnamed: RN14.14, U30.61
unnamed: RN14.15, U30.60
unnamed: RN14.16, U30.59
unnamed: RN13.15, U30.43
unnamed: RN13.13, U30.41
unnamed: CHG4.2, R65.1
unnamed: CHG4.1, D22.A
unnamed: D22.C, U34.1
unnamed: R66.2, U34.5
unnamed: I2C4.1, R70.2
unnamed: I2C4.3, R69.2
unnamed: J30.SHLD1, J30.SHLD2, J30.SHLD3, J30.SHLD4, J30.SHLD5, J30.SHLD6, J30.SHLD7, J30.SHLD8, SHLD4.2
unnamed: J30.B5, R67.2
unnamed: J30.A5, R68.2
unnamed: C119.1, U38.9
unnamed: C120.1, U38.64
unnamed: C123.2, R71.1, RN20.7
unnamed: R72.2, RN20.10, U38.25
unnamed: D25.C, R74.2
unnamed: JP5.2, R75.1
unnamed: D23.C, R75.2
unnamed: RN18.13, U38.67
unnamed: RN20.13, U38.19
unnamed: RN20.12, U38.20
unnamed: RN20.11, U38.21
unnamed: RN17.10, U38.57
unnamed: RN17.11, U38.56
unnamed: RN18.12, U38.68
unnamed: RN19.7, U38.94
unnamed: RN19.6, U38.95
unnamed: RN19.5, U38.96
unnamed: RN19.4, U38.97
unnamed: RN19.3, U38.98
unnamed: RN17.12, U38.48
unnamed: RN17.14, U38.42
unnamed: RN19.8, U38.93
unnamed: Q9.1, R76.2
unnamed: Q10.1, R77.2
unnamed: C132.1, C133.1, FB10.1, U38.87, U38.91
unnamed: BAT4.2, U38.8
unnamed: RN20.9, U38.36
unnamed: RN20.14, U38.18
unnamed: RN18.9, U38.92
unnamed: RN18.14, U38.61
unnamed: RN18.15, U38.60
unnamed: RN18.16, U38.59
unnamed: RN17.15, U38.43
unnamed: RN17.13, U38.41
unnamed: CHG5.2, R81.1
unnamed: CHG5.1, D27.A
unnamed: D27.C, U42.1
unnamed: R82.2, U42.5
unnamed: I2C5.1, R86.2
unnamed: I2C5.3, R85.2
unnamed: J37.SHLD1, J37.SHLD2, J37.SHLD3, J37.SHLD4, J37.SHLD5, J37.SHLD6, J37.SHLD7, J37.SHLD8, SHLD5.2
unnamed: J37.B5, R83.2
unnamed: J37.A5, R84.2
unnamed: C146.1, U46.9
unnamed: C147.1, U46.64
unnamed: C150.2, R87.1, RN24.7
unnamed: R88.2, RN24.10, U46.25
unnamed: D30.C, R90.2
unnamed: JP6.2, R91.1
unnamed: D28.C, R91.2
unnamed: RN22.13, U46.67
unnamed: RN24.13, U46.19
unnamed: RN24.12, U46.20
unnamed: RN24.11, U46.21
unnamed: RN21.10, U46.57
unnamed: RN21.11, U46.56
unnamed: RN22.12, U46.68
unnamed: RN23.7, U46.94
unnamed: RN23.6, U46.95
unnamed: RN23.5, U46.96
unnamed: RN23.4, U46.97
unnamed: RN23.3, U46.98
unnamed: RN21.12, U46.48
unnamed: RN21.14, U46.42
unnamed: RN23.8, U46.93
unnamed: Q11.1, R92.2
unnamed: Q12.1, R93.2
unnamed: C159.1, C160.1, FB12.1, U46.87, U46.91
unnamed: BAT5.2, U46.8
unnamed: RN24.9, U46.36
unnamed: RN24.14, U46.18
unnamed: RN22.9, U46.92
unnamed: RN22.14, U46.61
unnamed: RN22.15, U46.60
unnamed: RN22.16, U46.59
unnamed: RN21.15, U46.43
unnamed: RN21.13, U46.41
QIO0: U1.73, U5.5
QIO1: U1.74, U5.2
QIO2: U1.71, U5.3
QIO3: U1.72, U5.7
QIO4: U13.2, U14.74
QIO5: U13.5, U14.73
QIO6: U13.7, U14.72
QIO7: U13.3, U14.71
QIO8: U21.2, U22.74
QIO9: U21.5, U22.73
QIO10: U21.7, U22.72
QIO11: U21.3, U22.71
QIO12: U29.2, U30.74
QIO13: U29.5, U30.73
QIO14: U29.7, U30.72
QIO15: U29.3, U30.71
QIO16: U37.2, U38.74
QIO17: U37.5, U38.73
QIO18: U37.7, U38.72
QIO19: U37.3, U38.71
QIO20: U45.2, U46.74
QIO21: U45.5, U46.73
QIO22: U45.7, U46.72
QIO23: U45.3, U46.71
QSPCLK: U1.75, U5.6
QSPCLK1: U13.6, U14.75
QSPCLK2: U21.6, U22.75
QSPCLK3: U29.6, U30.75
QSPCLK4: U37.6, U38.75
QSPCLK5: U45.6, U46.75
RA6_SWCLK/TCK: J4.3, U1.50
RA6_SWCLK/TCK1: J13.3, U14.50
RA6_SWCLK/TCK2: J20.3, U22.50
RA6_SWCLK/TCK3: J27.3, U30.50
RA6_SWCLK/TCK4: J34.3, U38.50
RA6_SWCLK/TCK5: J41.3, U46.50
RA6_SWDIO/TMS: J4.2, U1.51
RA6_SWDIO/TMS1: J13.2, U14.51
RA6_SWDIO/TMS2: J20.2, U22.51
RA6_SWDIO/TMS3: J27.2, U30.51
RA6_SWDIO/TMS4: J34.2, U38.51
RA6_SWDIO/TMS5: J41.2, U46.51
RA6_SWO/TDO/PICO/D1: J8.17, J13.4, U14.52
RA6_SWO/TDO/PICO/D2: J15.17, J20.4, U22.52
RA6_SWO/TDO/PICO/D3: J22.17, J27.4, U30.52
RA6_SWO/TDO/PICO/D4: J29.17, J34.4, U38.52
RA6_SWO/TDO/PICO/D5: J36.17, J41.4, U46.52
RA6_SWO/TDO/PICO/D18: J2.17, J4.4, U1.52
RA6_TDI/POCI/D1: J8.16, U14.53
RA6_TDI/POCI/D2: J15.16, U22.53
RA6_TDI/POCI/D3: J22.16, U30.53
RA6_TDI/POCI/D4: J29.16, U38.53
RA6_TDI/POCI/D5: J36.16, U46.53
RA6_TDI/POCI/D17: J2.16, U1.53
RGB_DIN: D4.DI, U1.70
RGB_DIN1: D9.DI, U14.70
RGB_DIN2: D14.DI, U22.70
RGB_DIN3: D19.DI, U30.70
RGB_DIN4: D24.DI, U38.70
RGB_DIN5: D29.DI, U46.70
RGB_DOUT: D4.DO, TP1.1
RGB_DOUT1: D9.DO, TP11.1
RGB_DOUT2: D14.DO, TP21.1
RGB_DOUT3: D19.DO, TP31.1
RGB_DOUT4: D24.DO, TP41.1
RGB_DOUT5: D29.DO, TP51.1
RX_RA6/TX_DA1: TP16.1, U12.5, U14.66
RX_RA6/TX_DA2: TP26.1, U20.5, U22.66
RX_RA6/TX_DA3: TP36.1, U28.5, U30.66
RX_RA6/TX_DA4: TP46.1, U36.5, U38.66
RX_RA6/TX_DA5: TP56.1, U44.5, U46.66
RX_RA6/TX_DA14531: TP6.1, U1.66, U2.5
SCK/D1: J8.18, U14.54
SCK/D2: J15.18, U22.54
SCK/D3: J22.18, U30.54
SCK/D4: J29.18, U38.54
SCK/D5: J36.18, U46.54
SCK/D19: J2.18, U1.54
SCL/D1: J8.2, J11.4, R21.1, U11.7, U14.1
SCL/D2: J15.2, J18.4, R37.1, U19.7, U22.1
SCL/D3: J22.2, J25.4, R53.1, U27.7, U30.1
SCL/D4: J29.2, J32.4, R69.1, U35.7, U38.1
SCL/D5: J36.2, J39.4, R85.1, U43.7, U46.1
SCL/D16: J2.2, J3.4, R7.1, U1.1, U7.7
SDA/D1: J8.1, J11.3, R22.1, U11.8, U14.2
SDA/D2: J15.1, J18.3, R38.1, U19.8, U22.2
SDA/D3: J22.1, J25.3, R54.1, U27.8, U30.2
SDA/D4: J29.1, J32.3, R70.1, U35.8, U38.2
SDA/D5: J36.1, J39.3, R86.1, U43.8, U46.2
SDA/D15: J2.1, J3.3, R6.1, U1.2, U7.8
SDCLK: J7.5, U1.33
SDCLK1: J12.5, U14.33
SDCLK2: J19.5, U22.33
SDCLK3: J26.5, U30.33
SDCLK4: J33.5, U38.33
SDCLK5: J40.5, U46.33
SDCMD: J7.3, U1.34
SDCMD1: J12.3, U14.34
SDCMD2: J19.3, U22.34
SDCMD3: J26.3, U30.34
SDCMD4: J33.3, U38.34
SDCMD5: J40.3, U46.34
SDDAT0: J7.7, U1.37
SDDAT1: J7.8, U1.22
SDDAT2: J7.1, U1.31
SDDAT3: J7.2, U1.32
SDDAT4: J12.2, U14.32
SDDAT5: J12.1, U14.31
SDDAT6: J12.8, U14.22
SDDAT7: J12.7, U14.37
SDDAT8: J19.2, U22.32
SDDAT9: J19.1, U22.31
SDDAT10: J19.8, U22.22
SDDAT11: J19.7, U22.37
SDDAT12: J26.2, U30.32
SDDAT13: J26.1, U30.31
SDDAT14: J26.8, U30.22
SDDAT15: J26.7, U30.37
SDDAT16: J33.2, U38.32
SDDAT17: J33.1, U38.31
SDDAT18: J33.8, U38.22
SDDAT19: J33.7, U38.37
SDDAT20: J40.2, U46.32
SDDAT21: J40.1, U46.31
SDDAT22: J40.8, U46.22
SDDAT23: J40.7, U46.37
SDDET: J7.9, U1.35
SDDET1: J12.9, U14.35
SDDET2: J19.9, U22.35
SDDET3: J26.9, U30.35
SDDET4: J33.9, U38.35
SDDET5: J40.9, U46.35
STAT_LED: D2.A, U1.69
STAT_LED1: D10.A, U14.69
STAT_LED2: D15.A, U22.69
STAT_LED3: D20.A, U30.69
STAT_LED4: D25.A, U38.69
STAT_LED5: D30.A, U46.69
TX_RA6/RX_DA1: TP15.1, U12.14, U14.65
TX_RA6/RX_DA2: TP25.1, U20.14, U22.65
TX_RA6/RX_DA3: TP35.1, U28.14, U30.65
TX_RA6/RX_DA4: TP45.1, U36.14, U38.65
TX_RA6/RX_DA5: TP55.1, U44.14, U46.65
TX_RA6/RX_DA14531: TP5.1, U1.65, U2.14
UART_RX/D1: J8.15, U14.24
UART_RX/D2: J15.15, U22.24
UART_RX/D3: J22.15, U30.24
UART_RX/D4: J29.15, U38.24
UART_RX/D5: J36.15, U46.24
UART_RX/D21: J2.15, U1.24
UART_TX/D1: J8.14, U14.23
UART_TX/D2: J15.14, U22.23
UART_TX/D3: J22.14, U30.23
UART_TX/D4: J29.14, U38.23
UART_TX/D5: J36.14, U46.23
UART_TX/D20: J2.14, U1.23
USBD_N: D1.4, U1.27
USBD_N1: D3.4, U14.27
USBD_N2: D11.4, U22.27
USBD_N3: D16.4, U30.27
USBD_N4: D21.4, U38.27
USBD_N5: D26.4, U46.27
USBD_P: D1.6, U1.28
USBD_P1: D3.6, U14.28
USBD_P2: D11.6, U22.28
USBD_P3: D16.6, U30.28
USBD_P4: D21.6, U38.28
USBD_P5: D26.6, U46.28
USBIN_N: D1.3, J1.A7, J1.B7
USBIN_N1: D3.3, J9.A7, J9.B7
USBIN_N2: D11.3, J16.A7, J16.B7
USBIN_N3: D16.3, J23.A7, J23.B7
USBIN_N4: D21.3, J30.A7, J30.B7
USBIN_N5: D26.3, J37.A7, J37.B7
USBIN_P: D1.1, J1.A6, J1.B6
USBIN_P1: D3.1, J9.A6, J9.B6
USBIN_P2: D11.1, J16.A6, J16.B6
USBIN_P3: D16.1, J23.A6, J23.B6
USBIN_P4: D21.1, J30.A6, J30.B6
USBIN_P5: D26.1, J37.A6, J37.B6
VIN: C14.1, C17.1, C20.1, R10.2, U4.1, U6.1, U8.2, U8.7
VIN1: C41.1, C43.1, C45.1, R25.2, U9.1, U15.1, U16.2, U16.7
VIN2: C68.1, C70.1, C72.1, R41.2, U17.1, U23.1, U24.2, U24.7
VIN3: C95.1, C97.1, C99.1, R57.2, U25.1, U31.1, U32.2, U32.7
VIN4: C122.1, C124.1, C126.1, R73.2, U33.1, U39.1, U40.2, U40.7
VIN5: C149.1, C151.1, C153.1, R89.2, U41.1, U47.1, U48.2, U48.7
VREF1: C19.1, FB2.2, J2.26, U6.5
VREF2: C40.1, FB4.2, J8.26, U15.5
VREF3: C67.1, FB6.2, J15.26, U23.5
VREF4: C94.1, FB8.2, J22.26, U31.5
VREF5: C121.1, FB10.2, J29.26, U39.5
VREF6: C148.1, FB12.2, J36.26, U47.5
VREFEN: RN1.6, TP2.1, U1.76, U6.3
VREFEN1: RN6.6, TP12.1, U14.76, U15.3
VREFEN2: RN10.6, TP22.1, U22.76, U23.3
VREFEN3: RN14.6, TP32.1, U30.76, U31.3
VREFEN4: RN18.6, TP42.1, U38.76, U39.3
VREFEN5: RN22.6, TP52.1, U46.76, U47.3
VREG_EN: J2.11, R10.1, U4.3
VREG_EN1: J8.11, R25.1, U9.3
VREG_EN2: J15.11, R41.1, U17.3
VREG_EN3: J22.11, R57.1, U25.3
VREG_EN4: J29.11, R73.1, U33.3
VREG_EN5: J36.11, R89.1, U41.3
V_BATT: C15.1, C18.2, J2.12, J6.2, U3.3, U7.2, U7.3, U8.3
V_BATT1: C8.1, C30.2, J8.12, J10.2, U10.3, U11.2, U11.3, U16.3
V_BATT2: C56.1, C57.2, J15.12, J17.2, U18.3, U19.2, U19.3, U24.3
V_BATT3: C83.1, C84.2, J22.12, J24.2, U26.3, U27.2, U27.3, U32.3
V_BATT4: C110.1, C111.2, J29.12, J31.2, U34.3, U35.2, U35.3, U40.3
V_BATT5: C137.1, C138.2, J36.12, J38.2, U42.3, U43.2, U43.3, U48.3
V_USB: C13.1, D1.5, J1.VBUS1, J1.VBUS2, J2.10, R1.2, R9.2, U3.4, U8.6
V_USB1: C7.1, D3.5, J8.10, J9.VBUS1, J9.VBUS2, R17.2, R23.2, U10.4, U16.6
V_USB2: C55.1, D11.5, J15.10, J16.VBUS1, J16.VBUS2, R33.2, R39.2, U18.4, U24.6
V_USB3: C82.1, D16.5, J22.10, J23.VBUS1, J23.VBUS2, R49.2, R55.2, U26.4, U32.6
V_USB4: C109.1, D21.5, J29.10, J30.VBUS1, J30.VBUS2, R65.2, R71.2, U34.4, U40.6
V_USB5: C136.1, D26.5, J36.10, J37.VBUS1, J37.VBUS2, R81.2, R87.2, U42.4, U48.6
XCIN: C10.2, U1.10, Y2.P$1
XCIN1: C31.2, U14.10, Y3.P$1
XCIN2: C58.2, U22.10, Y5.P$1
XCIN3: C85.2, U30.10, Y7.P$1
XCIN4: C112.2, U38.10, Y9.P$1
XCIN5: C139.2, U46.10, Y11.P$1
XCOUT: C9.2, U1.11, Y2.P$2
XCOUT1: C32.2, U14.11, Y3.P$2
XCOUT2: C59.2, U22.11, Y5.P$2
XCOUT3: C86.2, U30.11, Y7.P$2
XCOUT4: C113.2, U38.11, Y9.P$2
XCOUT5: C140.2, U46.11, Y11.P$2
XTAL: U1.13, Y1.3
XTAL1: U14.13, Y4.3
XTAL2: U22.13, Y6.3
XTAL3: U30.13, Y8.3
XTAL4: U38.13, Y10.3
XTAL5: U46.13, Y12.3
